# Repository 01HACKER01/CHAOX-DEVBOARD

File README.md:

# CHAOX-DEVBOARD

## what is this 
so this is a devboard which can be used to make projects this devboard is made using the rp2040 

## why it exists 
so i wanted to make a simple thing and i saw teh guide for it so i thought lets make this and it can be used to make projects 

## how to assemble 
just add every comp in its place and use a hot air gun to solder them in place 

## how to flash 
1. Connect the board to your PC using a USB data cable.
2. Hold the BOOT button while connecting the USB cable.
3. Open File Explorer and look for the `RPI-RP2` drive.
4. Download or compile firmware as a `.uf2` file.
5. Drag and drop the `.uf2` file into the `RPI-RP2` drive.
6. The board will restart and run the firmware.

# BOM
| Designation | Comment | Quantity | Estimated Price (USD) | Link |
|---|---|---:|---:|---|
| C1, C10 | 1uF, 0402 | 2 | $0.02 | [Alibaba](https://www.alibaba.com/trade/search?SearchText=1uF+0402+ceramic+capacitor) |
| C13, C14 | 10uF, 0603 | 2 | $0.05 | [Alibaba](https://www.alibaba.com/trade/search?SearchText=10uF+0603+ceramic+capacitor) |
| C15, C16 | 33pF, 0402 | 2 | $0.02 | [Alibaba](https://www.alibaba.com/trade/search?SearchText=33pF+0402+ceramic+capacitor) |
| C2-C9, C11, C12, C17 | 0.1uF, 0402 | 11 | $0.10 | [Alibaba](https://www.alibaba.com/trade/search?SearchText=100nF+0402+ceramic+capacitor) |
| J1 | USB-C receptacle, 14-pin | 1 | $0.50 | [Alibaba](https://www.alibaba.com/trade/search?SearchText=USB+C+14Pin+HRO+TYPE-C-31-M-12) |
| J2, J3 | 1x20, 2.54mm pin headers | 2 | $0.40 | [Alibaba](https://www.alibaba.com/trade/search?SearchText=1x20+2.54mm+male+pin+header) |
| J4 | 1x03, 2.54mm pin header | 1 | $0.05 | [Alibaba](https://www.alibaba.com/trade/search?SearchText=1x3+2.54mm+male+pin+header) |
| R1, R2 | 5.1kΩ, 0402 | 2 | $0.02 | [Alibaba](https://www.alibaba.com/trade/search?SearchText=5.1K+0402+SMD+resistor) |
| R3, R4 | 27kΩ, 0402 | 2 | $0.02 | [Alibaba](https://www.alibaba.com/trade/search?SearchText=27K+0402+SMD+resistor) |
| R5, R6 | 1kΩ, 0402 | 2 | $0.02 | [Alibaba](https://www.alibaba.com/trade/search?SearchText=1K+0402+SMD+resistor) |
| R7 | 10kΩ, 0402 | 1 | $0.01 | [Alibaba](https://www.alibaba.com/trade/search?SearchText=10K+0402+SMD+resistor) |
| SW1 | SMD push button | 1 | $0.10 | [Alibaba](https://www.alibaba.com/trade/search?SearchText=SMD+SPST+NO+tactile+push+button) |
| U1 | RP2040 microcontroller | 1 | $1.10 | [Alibaba](https://www.alibaba.com/trade/search?SearchText=RP2040+microcontroller) |
| U2 | MCP1700 3.3V regulator, SOT-23 | 1 | $0.50 | [Alibaba](https://www.alibaba.com/trade/search?SearchText=MCP1700T-3302E) |
| U4 | W25Q16JVUXIQ TR flash memory | 1 | $1.18 | [Alibaba](https://www.alibaba.com/trade/search?SearchText=W25Q16JVUXIQTR) |
| Y2 | 12MHz, 3.2x2.5mm crystal | 1 | $0.15 | [Alibaba](https://www.alibaba.com/trade/search?SearchText=12MHz+3225+SMD+crystal) |
| PCB | Custom PCB fabrication | 1 board | $10.00 | [PCBWay](https://www.pcbway.com/) |
| **TOTAL** | **Components + 1 PCB** | | **≈ $14.24** ||
without shipping 

# thank you

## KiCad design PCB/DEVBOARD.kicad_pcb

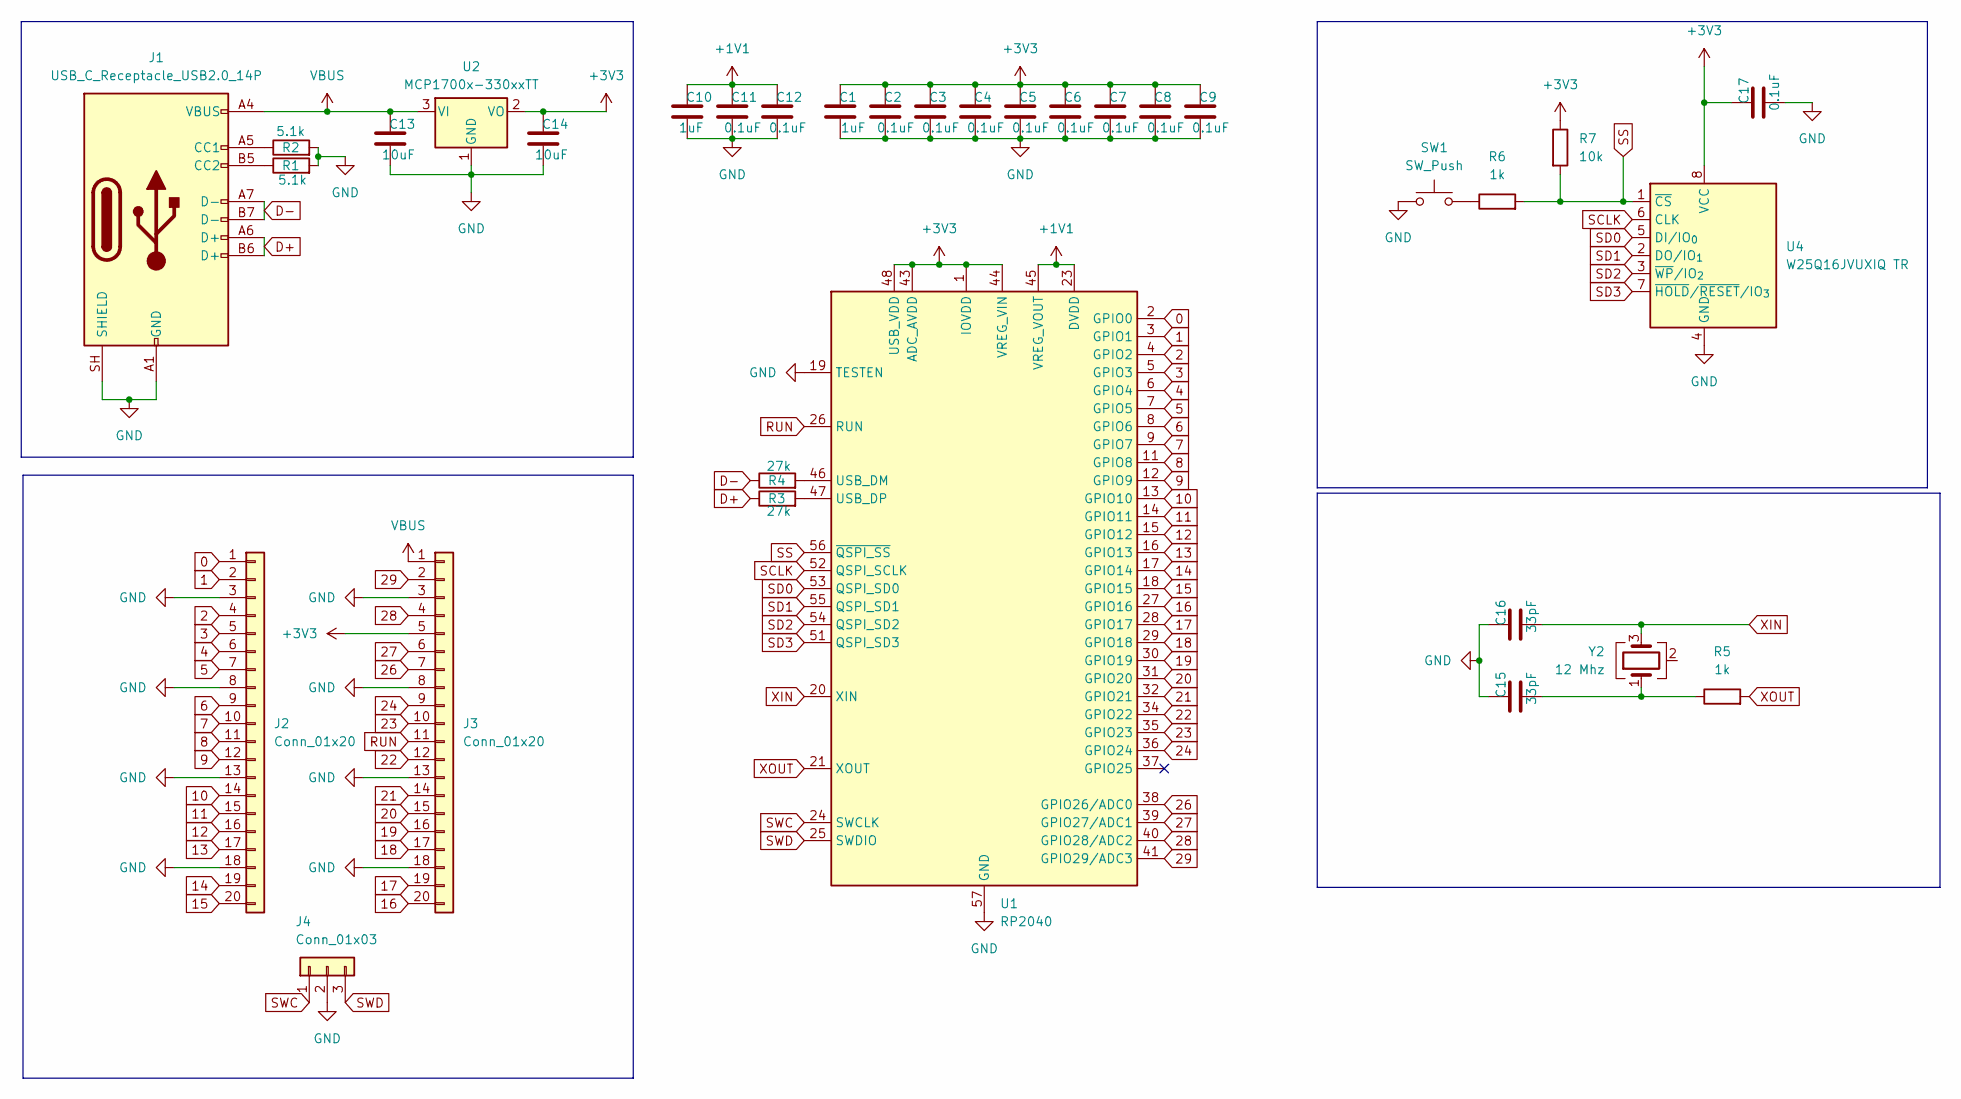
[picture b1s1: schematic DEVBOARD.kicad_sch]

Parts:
C1, C10: 1uF; C_0402_1005Metric
C2, C3, C4, C5, C6, C7, C8, C9, C11, C12, C17: 0.1uF; C_0402_1005Metric
C13, C14: 10uF; C_0603_1608Metric
C15, C16: 33pF; C_0402_1005Metric
J1: USB_C_Receptacle_USB2.0_14P; USB_C_Receptacle_HRO_TYPE-C-31-M-12
J2, J3: Conn_01x20; PinHeader_1x20_P2.54mm_Vertical
J4: Conn_01x03; PinHeader_1x03_P2.54mm_Vertical
R1, R2: 5.1k; R_0402_1005Metric
R3, R4: 27k; R_0402_1005Metric
R5, R6: 1k; R_0402_1005Metric
R7: 10k; R_0402_1005Metric
SW1: SW_Push; SW_Push_SPST_NO_Alps_SKRK
U1: RP2040; QFN-56-1EP_7x7mm_P0.4mm_EP3.2x3.2mm
U2: MCP1700x-330xxTT; SOT-23
U4: W25Q16JVUXIQ TR; Winbond_USON-8-1EP_3x2mm_P0.5mm_EP0.2x1.6mm
Y2: 12 Mhz; Crystal_SMD_3225-4Pin_3.2x2.5mm

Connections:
0: J2.1, U1.2 (GPIO0)
1: J2.2, U1.3 (GPIO1)
2: J2.4, U1.4 (GPIO2)
3: J2.5, U1.5 (GPIO3)
4: J2.6, U1.6 (GPIO4)
5: J2.7, U1.7 (GPIO5)
6: J2.9, U1.8 (GPIO6)
7: J2.10, U1.9 (GPIO7)
8: J2.11, U1.11 (GPIO8)
9: J2.12, U1.12 (GPIO9)
10: J2.14, U1.13 (GPIO10)
11: J2.15, U1.14 (GPIO11)
12: J2.16, U1.15 (GPIO12)
13: J2.17, U1.16 (GPIO13)
14: J2.19, U1.17 (GPIO14)
15: J2.20, U1.18 (GPIO15)
16: J3.20, U1.27 (GPIO16)
17: J3.19, U1.28 (GPIO17)
18: J3.17, U1.29 (GPIO18)
19: J3.16, U1.30 (GPIO19)
20: J3.15, U1.31 (GPIO20)
21: J3.14, U1.32 (GPIO21)
22: J3.12, U1.34 (GPIO22)
23: J3.10, U1.35 (GPIO23)
24: J3.9, U1.36 (GPIO24)
26: J3.7, U1.38 (GPIO26/ADC0)
27: J3.6, U1.39 (GPIO27/ADC1)
28: J3.4, U1.40 (GPIO28/ADC2)
29: J3.2, U1.41 (GPIO29/ADC3)
+1V1: C10.1, C11.1, C12.1, U1.23 (DVDD), U1.45 (VREG_VOUT), U1.50 (DVDD)
+3V3: C1.1, C2.1, C3.1, C4.1, C5.1, C6.1, C7.1, C8.1, C9.1, C14.1, C17.1, J3.5, R7.1, U1.1 (IOVDD), U1.10 (IOVDD), U1.22 (IOVDD), U1.33 (IOVDD), U1.42 (IOVDD), U1.43 (ADC_AVDD), U1.44 (VREG_VIN), U1.48 (USB_VDD), U1.49 (IOVDD), U2.2 (VO), U4.8 (VCC)
D+: J1.A6 (D+), J1.B6 (D+), R3.1
D-: J1.A7 (D-), J1.B7 (D-), R4.1
GND: C1.2, C2.2, C3.2, C4.2, C5.2, C6.2, C7.2, C8.2, C9.2, C10.2, C11.2, C12.2, C13.2, C14.2, C15.1, C16.1, C17.2, J1.A1 (GND), J1.A12 (GND), J1.B1 (GND), J1.B12 (GND), J1.SH (SHIELD), J2.3, J2.8, J2.13, J2.18, J3.3, J3.8, J3.13, J3.18, J4.2, R1.2, R2.2, SW1.1, U1.19 (TESTEN), U1.57 (GND), U2.1 (GND), U4.4 (GND)
unnamed: C15.2, R5.1, Y2.1
unnamed: J1.A5 (CC1), R2.1
unnamed: J1.B5 (CC2), R1.1
unnamed: R6.1, SW1.2
unnamed: R4.2, U1.46 (USB_DM)
unnamed: R3.2, U1.47 (USB_DP)
unnamed: Y2.2 (G), Y2.4 (G)
RUN: J3.11, U1.26 (RUN)
SCLK: U1.52 (QSPI_SCLK), U4.6 (CLK)
SD0: U1.53 (QSPI_SD0), U4.5 (DI/IO_{0})
SD1: U1.55 (QSPI_SD1), U4.2 (DO/IO_{1})
SD2: U1.54 (QSPI_SD2), U4.3 (~WP/IO_{2})
SD3: U1.51 (QSPI_SD3), U4.7 (~HOLD/~RESET/IO_{3})
SS: R6.2, R7.2, U1.56 (~QSPI_SS), U4.1 (~CS)
SWC: J4.1, U1.24 (SWCLK)
SWD: J4.3, U1.25 (SWDIO)
VBUS: C13.1, J1.A4 (VBUS), J1.A9 (VBUS), J1.B4 (VBUS), J1.B9 (VBUS), J3.1, U2.3 (VI)
XIN: C16.2, U1.20 (XIN), Y2.3
XOUT: R5.2, U1.21 (XOUT)

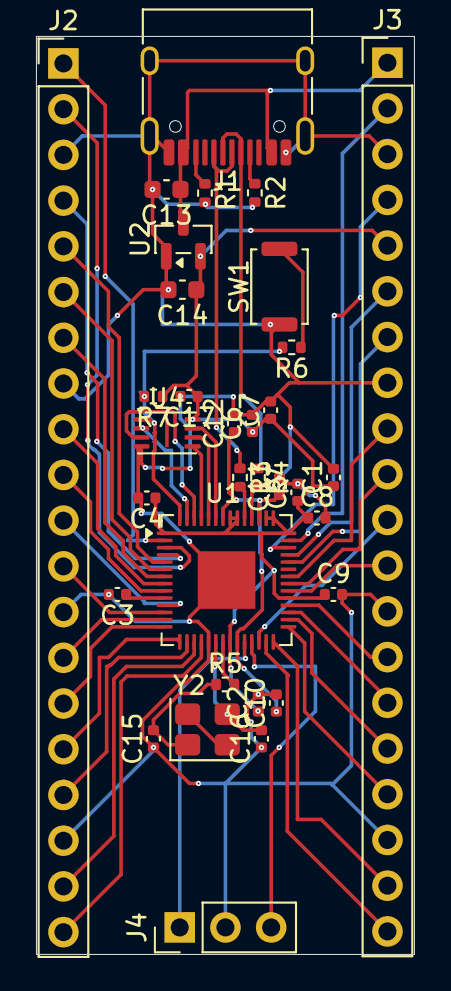
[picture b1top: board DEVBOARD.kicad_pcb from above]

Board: 2 copper layers, 21.0 x 51.0 mm, 33 parts (0 on the bottom side), 53 nets.
